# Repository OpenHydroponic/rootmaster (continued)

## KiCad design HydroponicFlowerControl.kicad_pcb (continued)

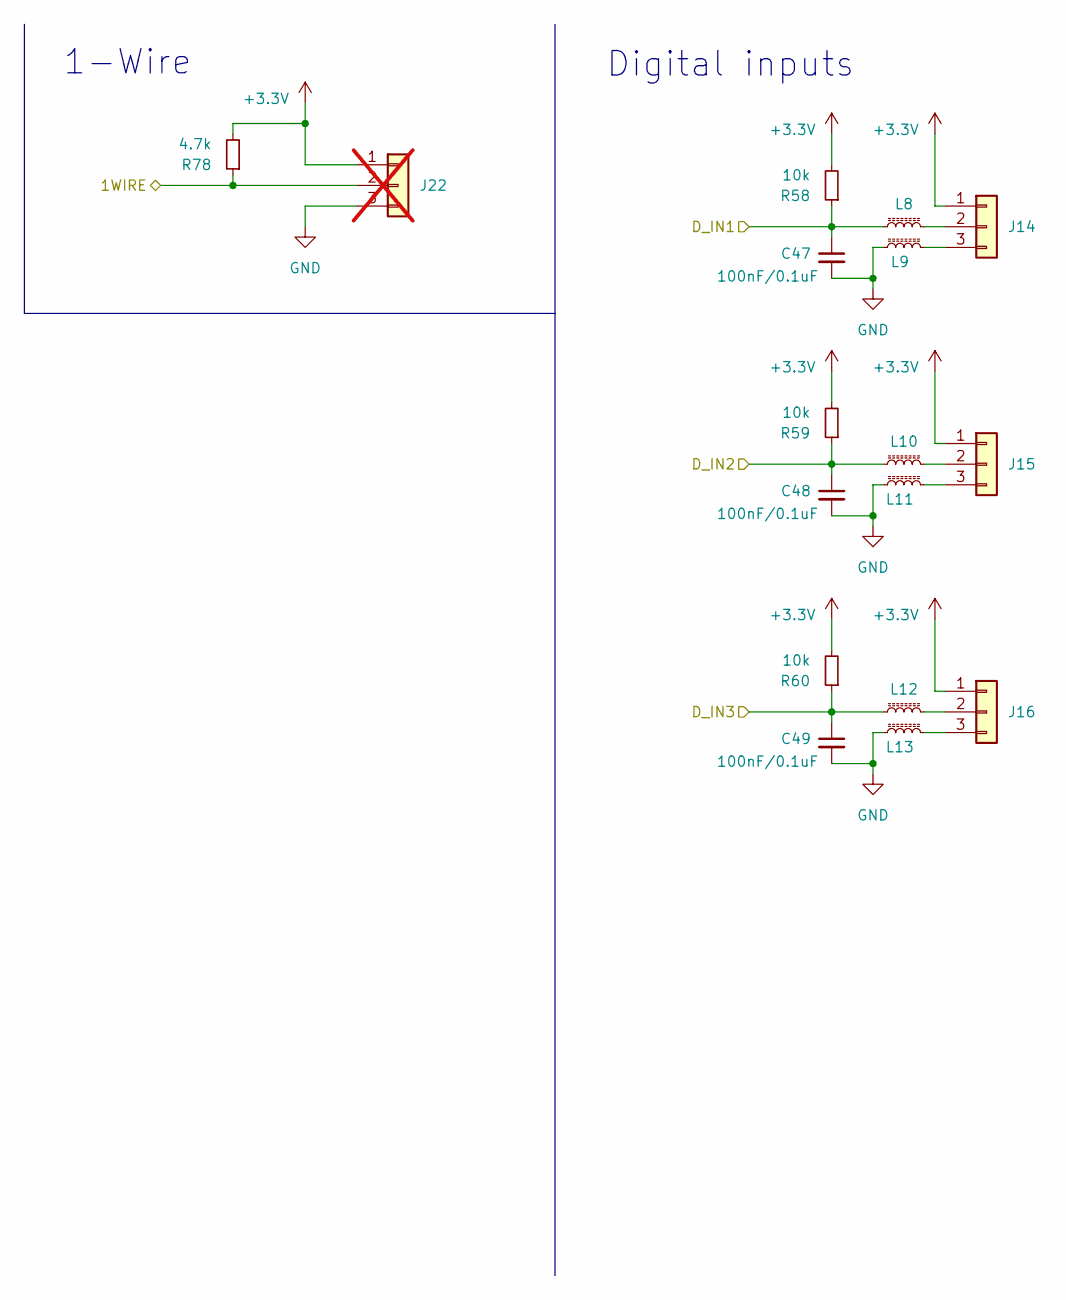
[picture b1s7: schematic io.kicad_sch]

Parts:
C47, C48, C49: 100nF/0.1uF; C_0603_1608Metric; LCSC C14663
J14, J15, J16: S3B-PH-K-S(LF)(SN); JST_PH_S3B-PH-K_1x03_P2.00mm_Horizontal; LCSC C157929
J22: 1-Wire; PinHeader_1x03_P2.54mm_Vertical; not fitted
L8, L9, L10, L11, L12, L13: L_Ferrite_Small; L_0603_1608Metric; LCSC C1002
R58, R59, R60: 10k; R_0603_1608Metric; LCSC C25804
R78: 4.7k; R_0603_1608Metric; LCSC C23162

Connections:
+3.3V: J14.1, J15.1, J16.1, J22.1, R58.2, R59.2, R60.2, R78.2; also elsewhere on the board
/IO/1WIRE: J22.2, R78.1; also elsewhere on the board
/IO/D_IN1: C47.1, L8.2, R58.1; also elsewhere on the board
/IO/D_IN2: C48.1, L10.2, R59.1; also elsewhere on the board
/IO/D_IN3: C49.1, L12.2, R60.1; also elsewhere on the board
GND: C47.2, C48.2, C49.2, J22.3, L9.2, L11.2, L13.2; also elsewhere on the board
unnamed: J14.2, L8.1
unnamed: J14.3, L9.1
unnamed: J15.2, L10.1
unnamed: J15.3, L11.1
unnamed: J16.2, L12.1
unnamed: J16.3, L13.1

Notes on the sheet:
Digital inputs
1-Wire

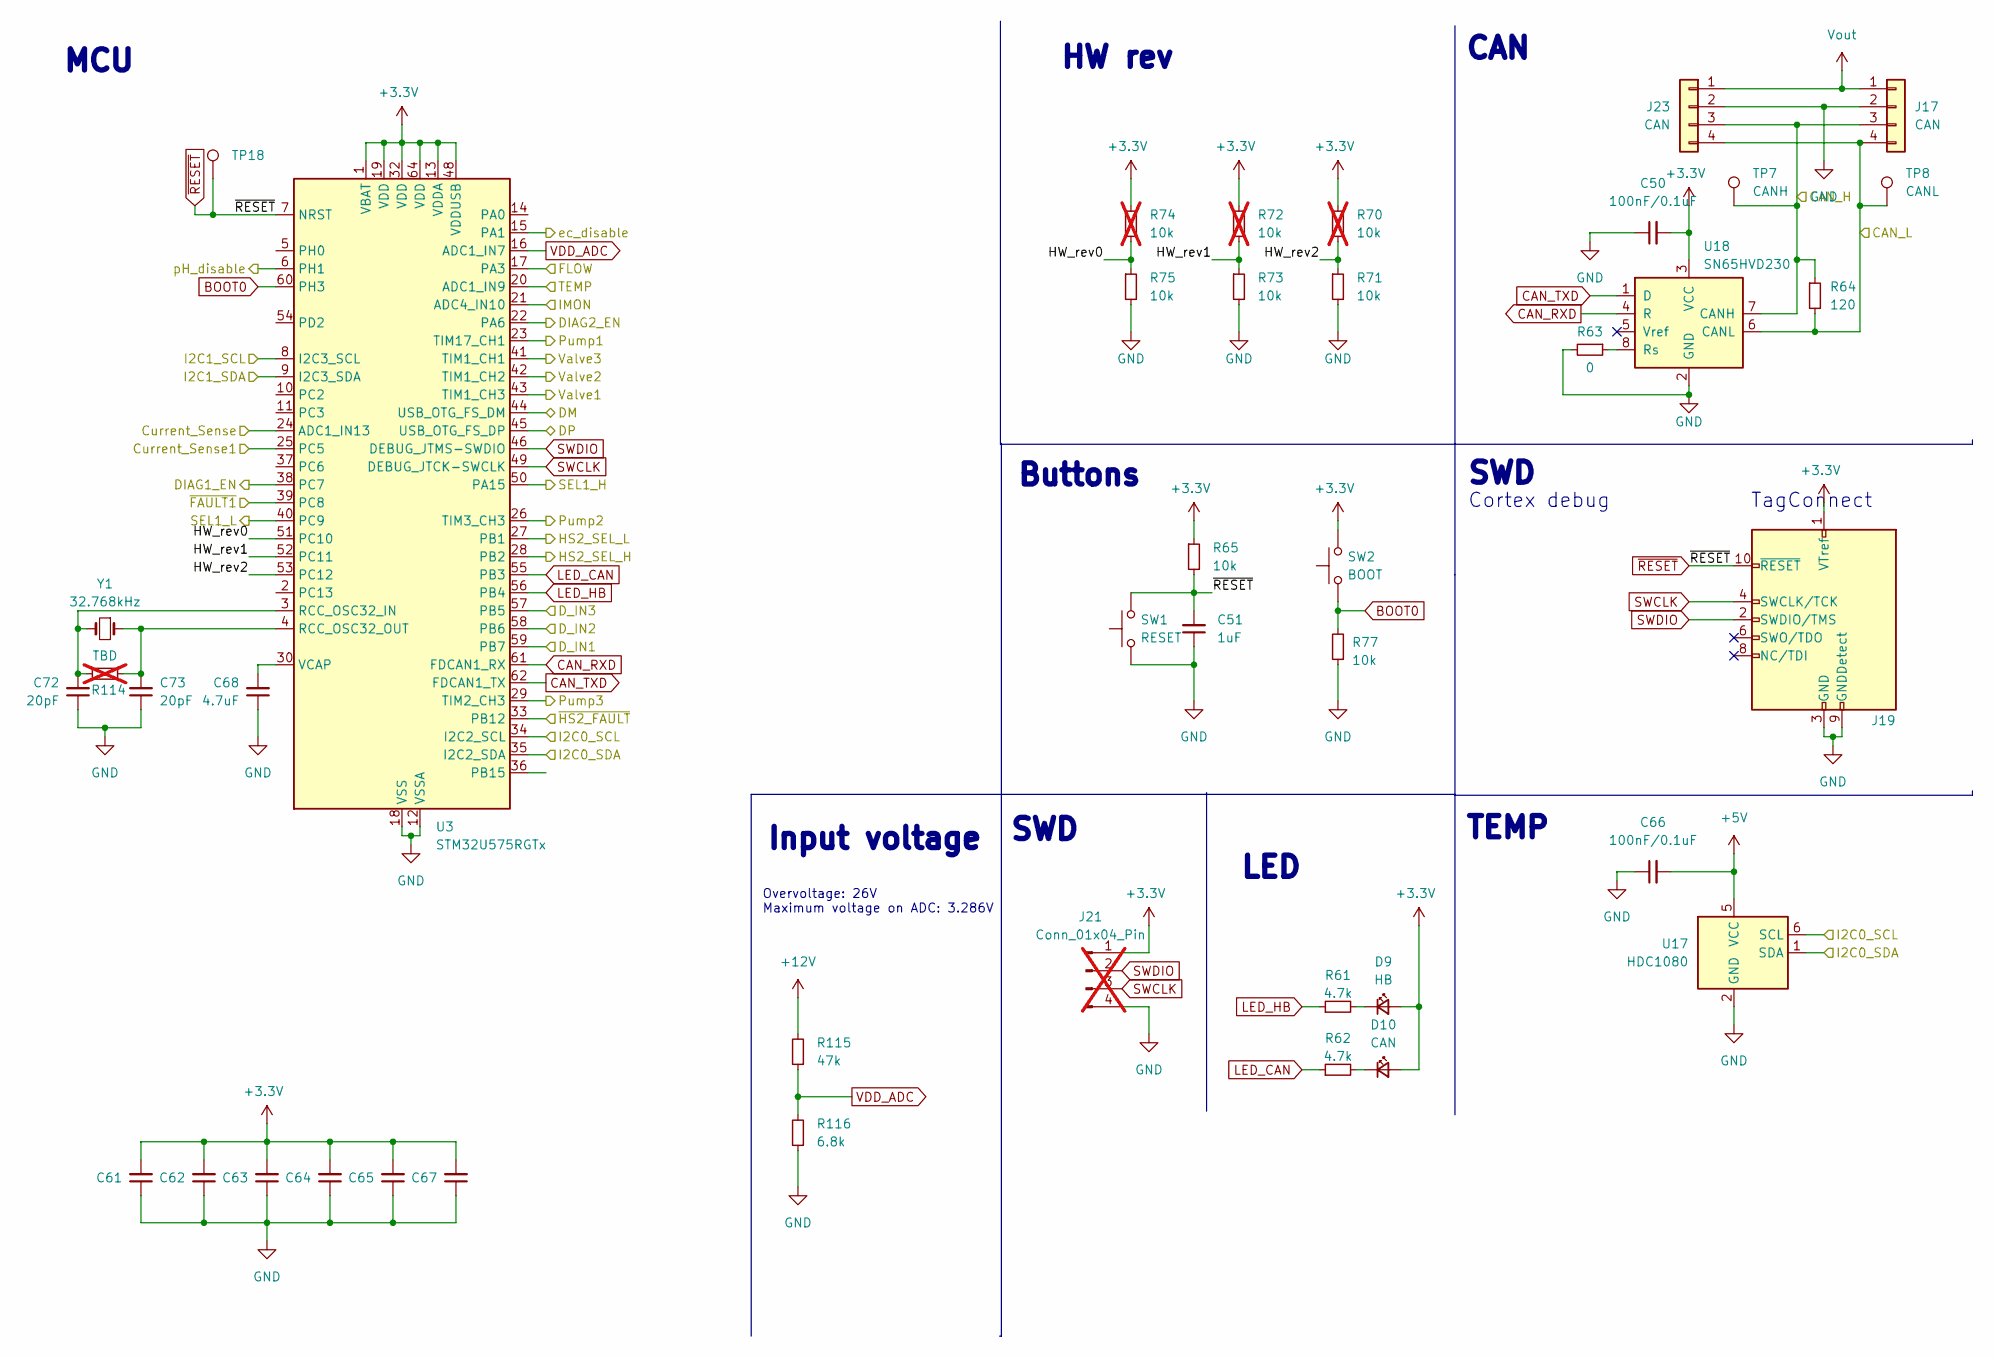
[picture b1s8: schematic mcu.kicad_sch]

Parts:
C50, C66: 100nF/0.1uF; C_0603_1608Metric; LCSC C14663
C51: 1uF; C_0603_1608Metric; LCSC C15849
C61, C62, C63, C64, C65, C67: 100nF/0.1uF; C_0402_1005Metric; LCSC C1525
C68: 4.7uF; C_0402_1005Metric; LCSC C23733
C72, C73: 20pF; C_0402_1005Metric; LCSC C1554
D9, D10: 100mW 120° 2.6V~3.1V 360mcd 5mA Yellow; LED_0603_1608Metric; LCSC C2290
J17, J23: CAN; AMASS_XT30PW(2+2); LCSC C19268030
J19: Conn_ARM_JTAG_SWD_10; Tag-Connect_TC2050-IDC-FP_2x05_P1.27mm_Vertical
J21: Conn_01x04_Pin; PinHeader_1x04_P2.54mm_Vertical; LCSC C6332197; not fitted
R61, R62: 4.7k; R_0603_1608Metric; LCSC C23162
R63: 0; R_0603_1608Metric; LCSC C21189
R64: 120; R_1206_3216Metric; LCSC C17909
R65, R77: 10k; R_0603_1608Metric; LCSC C25804
R70, R72, R74: 10k; R_0402_1005Metric; LCSC C25744; not fitted
R71, R73, R75: 10k; R_0402_1005Metric; LCSC C25744
R114: TBD; R_0402_1005Metric; not fitted
R115: 47k; R_0603_1608Metric; LCSC C25819
R116: 6.8k; R_0603_1608Metric; LCSC C23212
SW1, SW2: TS-1187A-B-A-B; SW_SPST_TL3342; LCSC C318884
TP7: CANH; TestPoint_Pad_D1.5mm
TP8: CANL; TestPoint_Pad_D1.5mm
TP18: Reset; TestPoint_Pad_D1.5mm
U3: STM32U575RGTx; LQFP-64_10x10mm_P0.5mm; LCSC C5270980
U17: HDC1080; Texas_PWSON-N6; LCSC C82227
U18: SN65HVD230; SOIC-8_3.9x4.9mm_P1.27mm; LCSC C12084
Y1: 32.768kHz; Crystal_SMD_3215-2Pin_3.2x1.5mm; LCSC C32346

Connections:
+3.3V: C50.2, C61.2, C62.2, C63.2, C64.2, C65.2, C67.2, D9.2 (A), D10.2 (A), J19.1 (VTref), J21.1, R65.1, R70.1, R72.1, R74.1, SW2.2, U3.1 (VBAT), U3.13 (VDDA), U3.19 (VDD), U3.32 (VDD), U3.48 (VDDUSB), U3.64 (VDD), U18.3 (VCC); also elsewhere on the board
+5V: C66.2, U17.5 (VCC); also elsewhere on the board
+12V: R115.2; also elsewhere on the board
/EC/DISABLE: U3.15 (PA1); also elsewhere on the board
/EC/SCL: U3.34 (I2C2_SCL), U17.6 (SCL); also elsewhere on the board
/EC/SDA: U3.35 (I2C2_SDA), U17.1 (SDA); also elsewhere on the board
/Flow control/Current_Sense1: U3.25 (PC5); also elsewhere on the board
/Flow control/Current_Sense2: U3.24 (ADC1_IN13); also elsewhere on the board
/Flow control/DIAG1_EN: U3.38 (PC7); also elsewhere on the board
/Flow control/DIAG2_EN: U3.22 (PA6); also elsewhere on the board
/Flow control/FLOW: U3.17 (PA3); also elsewhere on the board
/Flow control/Pump1: U3.23 (TIM17_CH1); also elsewhere on the board
/Flow control/Pump2: U3.26 (TIM3_CH3); also elsewhere on the board
/Flow control/Pump3: U3.29 (TIM2_CH3); also elsewhere on the board
/Flow control/SEL1_H: U3.50 (PA15); also elsewhere on the board
/Flow control/SEL1_L: U3.40 (PC9); also elsewhere on the board
/Flow control/SEL2_H: U3.28 (PB2); also elsewhere on the board
/Flow control/SEL2_L: U3.27 (PB1); also elsewhere on the board
/Flow control/TEMP: U3.20 (ADC1_IN9); also elsewhere on the board
/Flow control/Valve1: U3.43 (TIM1_CH3); also elsewhere on the board
/Flow control/Valve2: U3.42 (TIM1_CH2); also elsewhere on the board
/Flow control/Valve3: U3.41 (TIM1_CH1); also elsewhere on the board
/Flow control/~FAULT1: U3.39 (PC8); also elsewhere on the board
/Flow control/~FAULT2: U3.33 (PB12); also elsewhere on the board
/IO/D_IN1: U3.59 (PB7); also elsewhere on the board
/IO/D_IN2: U3.58 (PB6); also elsewhere on the board
/IO/D_IN3: U3.57 (PB5); also elsewhere on the board
/MCU/CAN_H: J17.3, J23.3, R64.1, TP7.1 (1_1), U18.7 (CANH); also elsewhere on the board
/MCU/CAN_L: J17.4, J23.4, R64.2, TP8.1 (1_1), U18.6 (CANL); also elsewhere on the board
/MCU/HW_rev0: R74.2, R75.1, U3.51 (PC10)
/MCU/HW_rev1: R72.2, R73.1, U3.52 (PC11)
/MCU/HW_rev2: R70.2, R71.1, U3.53 (PC12)
/MCU/I2C1_SCL: U3.8 (I2C3_SCL); also elsewhere on the board
/MCU/I2C1_SDA: U3.9 (I2C3_SDA); also elsewhere on the board
/MCU/IMON: U3.21 (ADC4_IN10); also elsewhere on the board
/MCU/pH_disable: U3.6 (PH1); also elsewhere on the board
/Power/USB_D+: U3.45 (USB_OTG_FS_DP); also elsewhere on the board
/Power/USB_D-: U3.44 (USB_OTG_FS_DM); also elsewhere on the board
BOOT0: R77.2, SW2.1, U3.60 (PH3)
CAN_RXD: U3.61 (FDCAN1_RX), U18.4 (R)
CAN_TXD: U3.62 (FDCAN1_TX), U18.1 (D)
GND: C50.1, C51.1, C61.1, C62.1, C63.1, C64.1, C65.1, C66.1, C67.1, C68.1, C72.1, C73.1, J17.2, J19.3 (GND), J19.5 (GND), J19.9 (GNDDetect), J21.4, J23.2, R63.2, R71.2, R73.2, R75.2, R77.1, R116.1, SW1.1, U3.12 (VSSA), U3.18 (VSS), U3.31 (VSS), U3.47 (VSS), U3.63 (VSS), U17.2 (GND), U18.2 (GND); also elsewhere on the board
LED_CAN: R62.1, U3.55 (PB3)
LED_HB: R61.1, U3.56 (PB4)
unnamed: D9.1 (K), R61.2
unnamed: D10.1 (K), R62.2
unnamed: C72.2, R114.1, U3.3 (RCC_OSC32_IN), Y1.2
unnamed: C73.2, R114.2, U3.4 (RCC_OSC32_OUT), Y1.1
unnamed: C68.2, U3.30 (VCAP)
unnamed: R63.1, U18.8 (Rs)
SWCLK: J19.4 (SWCLK/TCK), J21.3, U3.49 (DEBUG_JTCK-SWCLK)
SWDIO: J19.2 (SWDIO/TMS), J21.2, U3.46 (DEBUG_JTMS-SWDIO)
VDD_ADC: R115.1, R116.2, U3.16 (ADC1_IN7)
Vout: J17.1, J23.1; also elsewhere on the board
~RESET: C51.2, J19.10 (~RESET), R65.2, SW1.2, TP18.1 (1_1), U3.7 (NRST)

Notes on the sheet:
TEMP
Buttons
SWD
HW rev
LED
Overvoltage: 26V Maximum voltage on ADC: 3.286V
TagConnect
MCU
CAN
Cortex debug
Input voltage

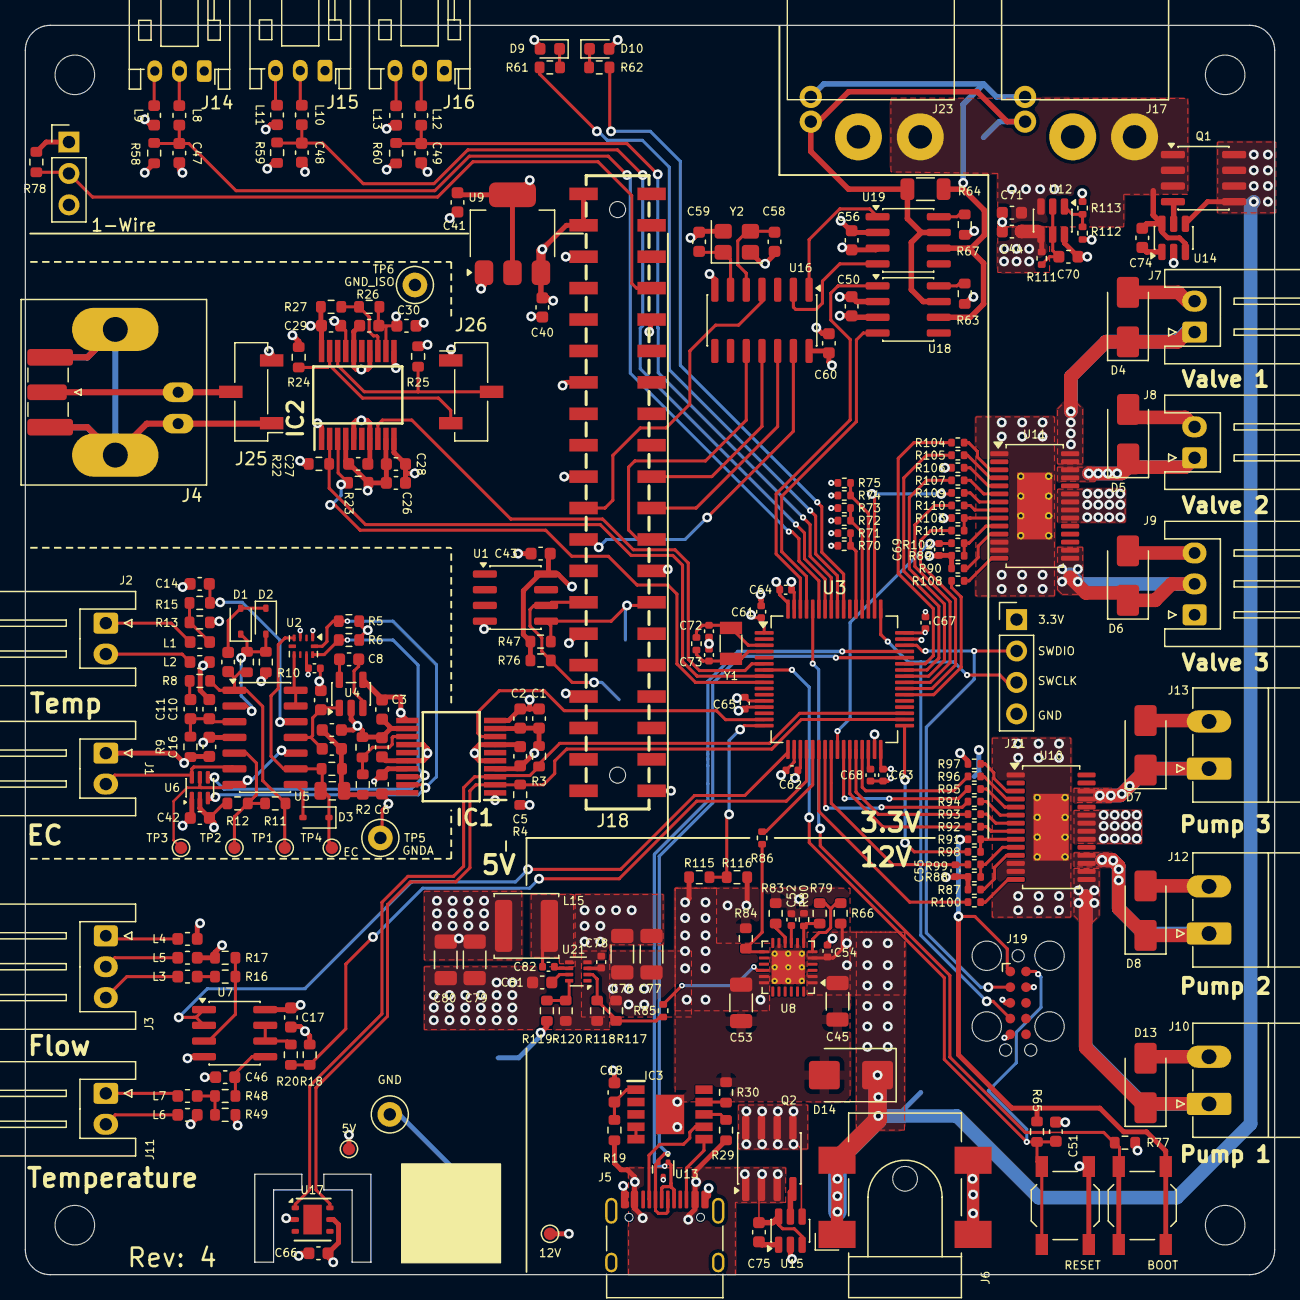
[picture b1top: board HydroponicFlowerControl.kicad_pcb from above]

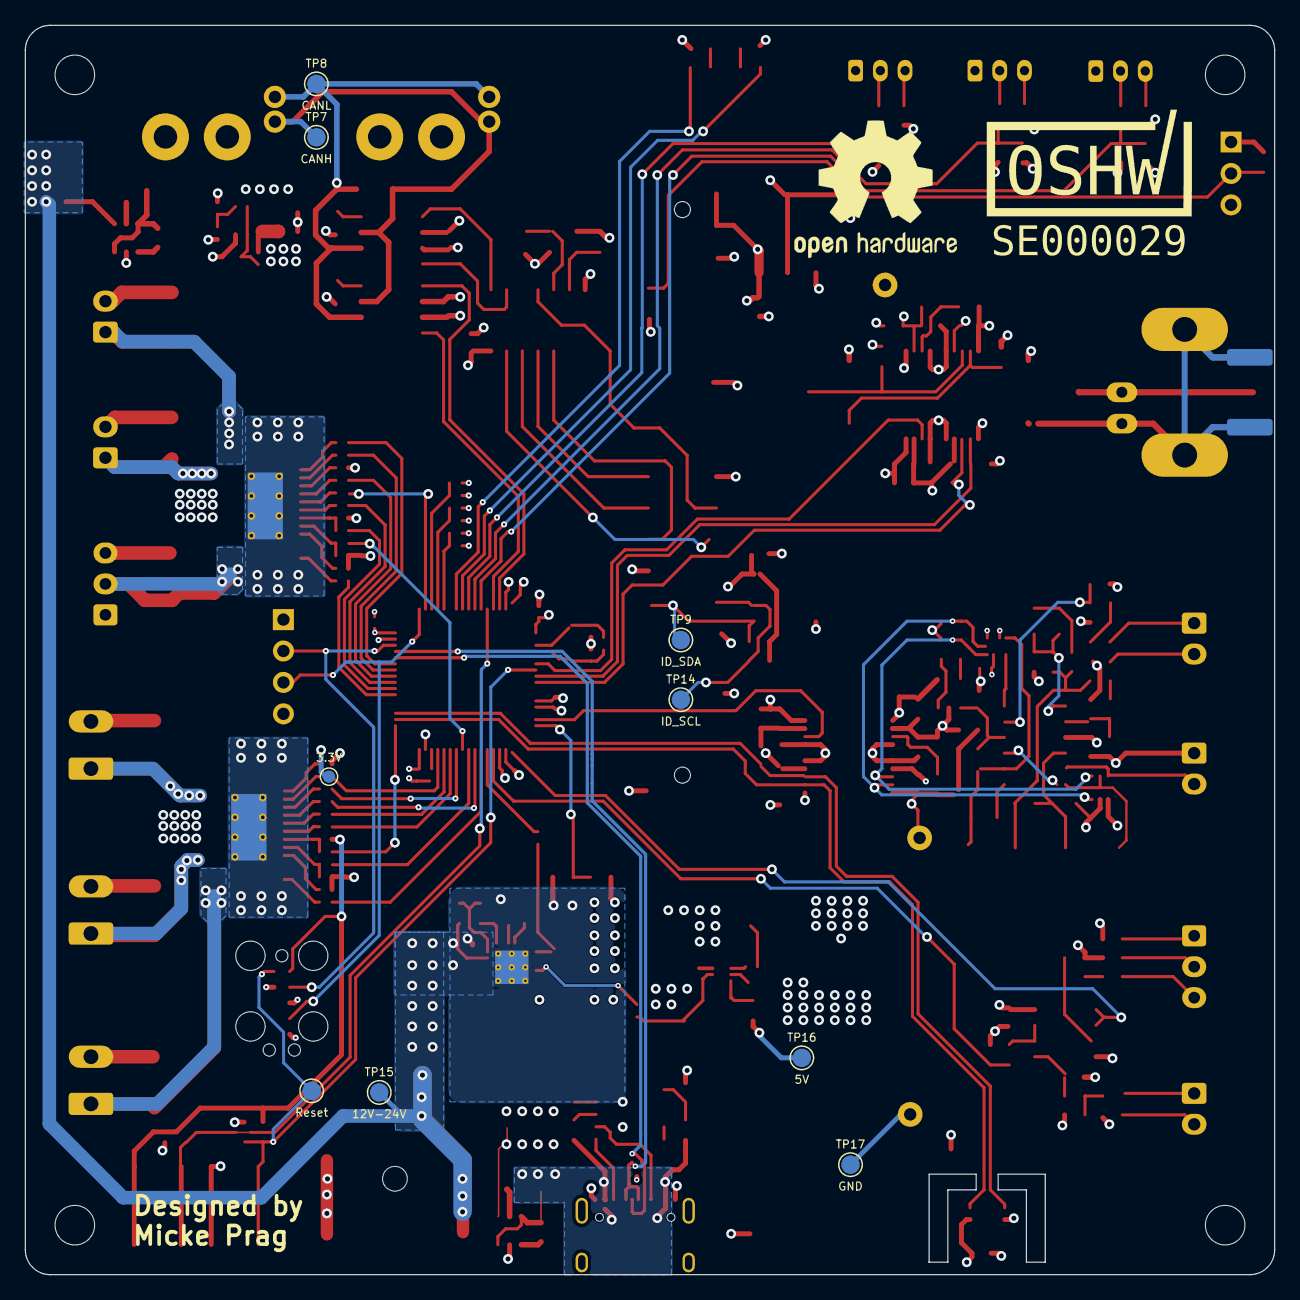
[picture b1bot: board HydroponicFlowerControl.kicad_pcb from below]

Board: 4 copper layers, 101.0 x 101.0 mm, 254 parts (9 on the bottom side), 165 nets.

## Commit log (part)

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2024-06-08 Initial import
2024-06-08 Add title to all schematics pages
2024-06-10 Add revision resistors
2024-06-10 Redesign board to fit within 102mm x 102mm
2024-10-27 Update BOM list fields
2024-10-27 Update step file with r1
2024-10-27 Decrease size of raspberry pi mounting holes
2024-10-27 Add disable signals for ec and ph
2024-10-27 Update max current for motor controller
    Closes #8
2024-10-27 Switch isolators to ADM3260
    Change pH isolator
    Closes #1
2024-10-27 Switch isolators to ADM3260
    Change EC isolator.
    See #1
2024-10-27 Update production data
2024-10-27 Add keepout zone for copper fills around temp sensor
2024-10-27 Update drc exclusions
2024-10-27 Swap source and drain on mosfets
    Closes #4
2024-10-28 Replace motor controller with mosfets instead
    Closes #21
2024-10-28 Replace RPi connector
    New variant is SMD type and has been rotated.
    Closes #16 and #11
2024-10-28 Add Cortex debug connector
    Closes #17
2024-10-29 Tie boot0 (PB8) to GND
    Closes #2
2024-10-29 Add RPi ID EEPROM
    Closes #15
2024-10-29 Switch to basic components for 5V LDO feedback
2024-11-03 Fix manufaturing properties
    Such as rotations
2024-11-03 Move R15 and R48 to the right side of the divider
    Closes #6
2024-11-03 Optimize EC RC filter
    Closes #5
2024-11-03 Protect PH_OUT from going out of bounds
    Closes #7
2024-11-08 Replace DC connector with SMD variant
    Closes #23
2024-11-08 Add testpoints for power and gnd
    Closes #3
2024-11-08 Route USB data signals to STM32
    The CANbus needed to be moved together with ec and ph disable signals.
    Closes #14 and #9
2024-11-08 Replace C57
    With a variant that can be used with economy pcbs at JLCPCB
    Closes #25
2024-11-08 Name the pins in the MCU after its actual function used
2024-11-08 Replace the mcu to a STM32G473 variant
2024-11-08 Connect button to BOOT0
    This is used to enter DFU bootloader
    Closes #26
2024-11-08 Add standard pinheaders for programming
    Pinout same as STM32 Blue pill
2024-11-08 Align pH connector
    See #10
2024-11-08 Align all connectors
    Closes #10
2024-11-08 Add power out to the digital inputs
    Closes #18
2024-11-08 Update rev to 2
    Closes #27
2024-11-08 Fix some manufacturing attributes for JLCPCB
2024-11-12 Fix ERC warnings
    See #28
2024-11-12 Add missing rotation offset attribute
2024-11-12 Fix ERC errors
    Closes #28
2024-11-12 Align connector silkscreen
    See #10
2024-11-12 Add 1-Wire
    Closes #29
2024-11-20 Add release job to generate schematics
2024-12-06 Remove step file
    It is now part of the release instead
2024-12-06 Add enclosure model
2024-12-06 Add LICENSE
2024-12-13 Add README
2025-01-14 Fix silkscreen overlap issues in board
2025-01-14 Move buttons
    Closes #45
2025-01-14 Add serial number QR
    Closes #46
2025-01-14 Move Cortex debug to get easier access to TagConnect
    Else it is quite hard to insert or remove the TagConnect
2025-01-14 Bump HW rev
    Closes #43
2025-01-14 Add dampening on NTC temp signal
    STM32 input is not 5V tolerant so the signal is lowered to 3.3V
    Closes #36
2025-01-14 Remove pH circuits
    And replace with a header to connect to an external HAT board
    Closes #40
2025-01-14 Remove TPS60400 (U11) from pH block
    Closes #30
2025-01-14 Add OSHW logo
    Closes #37
2025-01-14 Cleanup tracks
    Closes #32
2025-01-14 Add combined footprint for BNC and SMA
2025-01-14 Update pH connector to combined BNC and SMA footprint
2025-01-14 Rotate RPi
    Closes #44
2025-01-14 Connect GND on DC barrel jack
    Closes #35
2025-01-16 Cleanup tracks
2025-01-16 Replace footprint for J18
    Closes #31
2025-01-16 Update footprint for U13
    Closes #33
2025-01-17 Update part for JST 2P connectors
    Closes #41
2025-01-17 Add testpoints
    Closes #47
2025-01-17 Update manufacturing positions and rotations of parts
2025-01-17 Include THT components in manufacturing
2025-01-17 Align buttons
2025-01-17 Update revision to 3
    Closes #38
2025-01-17 Add designed by label
2025-11-13 Remove 8 MHz crystal
    Closes #51
2025-11-13 Hide Raspberry Pi 3d model
2025-11-17 Increase input voltage range to 10-35V
    See #52
2025-11-17 Replace MCU with STM32U575RGT
    Closes #49
2025-11-17 Increase size of inductor L14 to allow more power on the 5V rail
    See #52
2025-11-26 Add Reverse polarity protection
    Closes #55
2025-12-02 Replace 4 of the 6 highside outputs with TPS4H160B
    See #50
2025-12-02 Remove unused symbol ADUM6010ARSZ_0_1
2025-12-02 Add missing 3d model of DC barrel jack
2025-12-04 Replace the last 2 of the highside outputs with TPS4H160B
    Closes #50
2025-12-04 Add missing footprint SOP65P780X200-20N
2025-12-05 Add a second CAN connector
    Closes #58
2025-12-08 Protect CAN connector from over voltage
    Closes #57
2025-12-08 Add 32kHz crystal for RTC
    Closes #12
2025-12-08 Add ADC for input voltage
    Closes #59
2025-12-14 Resaved all files with KiCad 9.0.6
2026-03-31 Add production files to .gitignore
2026-04-03 Replace diode for Vin from CAN with ideal diode
    See #63
2026-04-03 Replace diode for USB power with ideal diode
    Closes #63
2026-04-03 Replace 5V stepdown with TPS62933
    Closes #64
2026-04-03 Replace TPS26630 with TPS16630
    Without reverse polarity protection (1 Dollar cheaper)
    Closes #62
2026-04-04 Upgrade BarrelJAck to a 24V 5A version
    Closes #56
2026-04-05 Fix mismatch between inputs to highside switches and outputs
    Closes #60
2026-04-09 Change pH pinsocket connector from THT to SMD
    Closes #42
2026-04-10 Update fabrication properties
2026-04-10 Replace TVS diode SMBJ28A with SMBJ28CA
    Unidirectional -> Bidirectional
2026-04-10 Change package if ADS1115 ADC Smaller, in stock and cheaper
2026-04-15 Revision 4
